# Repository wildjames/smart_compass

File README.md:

# Smart Compass

The product is going to be something similar to the compass in the Pirates of the Caribbean.

It has a ring of LEDs that indicate the direction you need to walk in to get to the place you want to be, which can be other devices in a tracking group, waypoints on a navigation route (e.g. hiking), Atlas Obscura sites for the city you're in, or some location you pinned (e.g. where you parked your car, or something like that).
Locations will be either pins dropped by the compass itself, or loaded to the device using a companion app on a phone - communicating with that means the device needs BLE. The nRF52840 module gives that.

The compass has a GNSS module for getting its own location, and a 9-axis IMU for the compass orientation.
It has a LoRa radio for kilometer-range mesh networking, allowing it to maintain an off-grid communication layer in cases where the cell network is either unavailable (e.g. rural locations, mountains), or overloaded (e.g. music festivals and other large events) - or if you just don't want to be carrying a phone (e.g. a kid being set loose in a shopping centre).

For typical single-device operation, however, the compass will rely on a companion phone app. Using the app, the user can navigate to desired location without referring to their phone. These can be user-defined, like setting the navigation destination on Maps, or get a list of Locations of Interest (LoI) from something like Atlas Obscura. I could also do a "hot/cold" thing with phone RSSI signal strength to get a kind of phone finder feature, but that may not be very useful.

## Design requirements

The device has a few core requirements:

- It must operate with no companion phone or PC. It's fine to have a phone for initial setup, or for additional features, but peer-to-peer operation must be entirely on-device.
- Tracking must be done by the device. The GNSS network must be used for this.
- The device must be secure - there must be no way for non-paired devices to be able to discern the location of a device, even if they are part of the same mesh network.
- Communication between devices must be long-range. Kilometer ranges between peers is a requirement, and longer ranges with a mesh network is also necessary.
- The battery must last for at least a day, but 3 day battery life is the target. Deep sleep, low power, and high polling modes should be used to assist this.
- The device must be handheld. No external antenna is ideal, but the option to add one may be worthwhile.
- The device must have flash storage
- The device needs an on-board way to communicate the direction and distance of paired devices.
  - The device must have a ring of addressable RGB LEDs for peer indication.
  - The device must have a haptic engine for feedback
  - The device may have a speaker for feedback.

I'm writing down user flows as I think of them in the [User Flow Library](UserFlowLibrary.md) page.

-----

## Archived KiCAD packages

- 0.1: First edition.
- 0.2: Submitted to reddit for hope of review. First hierarchical schematic.
- 0.3: Reviewed connections, fixed a few bugs with USB and SPI.
- 0.4: Rerouted the board to place the e-ink connector correctly, and the MCU more centrally. Also made the antenna placement more seriously, with proper clearance zone and via stitching.

-----

## Thoughts

The component cost per device is up to ~£50. The boards are about £5 per board for the first run (some heavy discounts, I shouldn't squander that). Assembled, the first shipment of 5 boards would cost $115 plus ~$60 in components per board makes that up to $400. That's a hefty chunk of cash. I could try getting just two assembled for this initial run, which brings it down to like, $200, but that's still pricey.

## TODO list

- Breaking the LED ring and display out to daughter boards is in progress. The two new schematics exist at [boards/led_ring/](boards/led_ring/) and [boards/display/](boards/display/); see [boards/README.md](boards/README.md) for the interconnect pinouts and what still has to be stripped out of the main board.
  - Similarly, it may be worth breaking the LoRa and GNSS out to a daughter board, which may make the antenna placement easier. Less compelling though, and probably not worth the extra thickness.
- I can apparently use a pi pico 2 as an SWD programmer, to flash the bootloader, and from there I can just upload via the native USB. I need to prove this out though.
- I will do the programming in Rust, using the Embassy ecosystem. This will give me the memory safety and speed of rust (nice when there is no easy way to see crashes on the device), but also the fearless concurrency will be a massive boon with all the ICs that need to be interfaced with.

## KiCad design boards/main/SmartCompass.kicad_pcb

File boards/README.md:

# Board set

The Smart Compass is built as three PCBs. KiCad has no multi-board project, so
each one is its own project directory here, and the parts they share live in
`../libs/`.

| Directory | Project | What it is |
| --------- | ------- | ---------- |
| `main/` | `SmartCompass` | The engine board: MCU, GNSS, LoRa, IMU, flash, power tree, haptics, buttons, USB |
| `led_ring/` | `LedRing` | The 16-LED addressable RGB ring |
| `display/` | `Display` | The e-ink panel connector and its charge-pump support |

The ring and display were split off so the housing can be assembled and
modified without the main board's position dictating where they sit.

Parts that are not on any board - the haptic actuator, the panel, the cell, the
case switches and buttons, the antennas, and the cables and housings joining
them - are listed in [EXTRA_PARTS_BOM.md](EXTRA_PARTS_BOM.md), because they never
appear in a BOM exported from a schematic. Outstanding sourcing work and open
risks are in [COMPONENT_SOURCING.md](COMPONENT_SOURCING.md).

The main board's power tree can be simulated in KiCad's built-in SPICE
simulator; [main/sim/README.md](main/sim/README.md) explains the setup, what is
modelled and excluded, and the results so far. The part models are in
`../libs/spice/`.

## Libraries

`../libs/smart_compass.kicad_sym` and `../libs/smart_compass.pretty` hold the
parts the boards share. They were extracted from the main board, where they had
only ever existed embedded inside the `.kicad_sch` and `.kicad_pcb` files - they
were never in any library table, so a new project could not place them.

Footprints live alongside in `../libs/smart_compass.pretty/`, and 3D models in
`../libs/smart_compass.3dshapes/`.

3D models are referenced from inside the footprint with a
`${KIPRJMOD}/../../libs/smart_compass.3dshapes/...` path
The main board still resolves its other custom parts from its embedded copies,
which is why its ERC reports a long list of "configuration does not include
the symbol library" warnings. Those predate the split. Extracting the rest
into `libs/` would clear them.

Each daughter board has a project-scope `sym-lib-table` and `fp-lib-table`
pointing at `${KIPRJMOD}/../../libs/`, so the paths survive the repo being
cloned somewhere else.

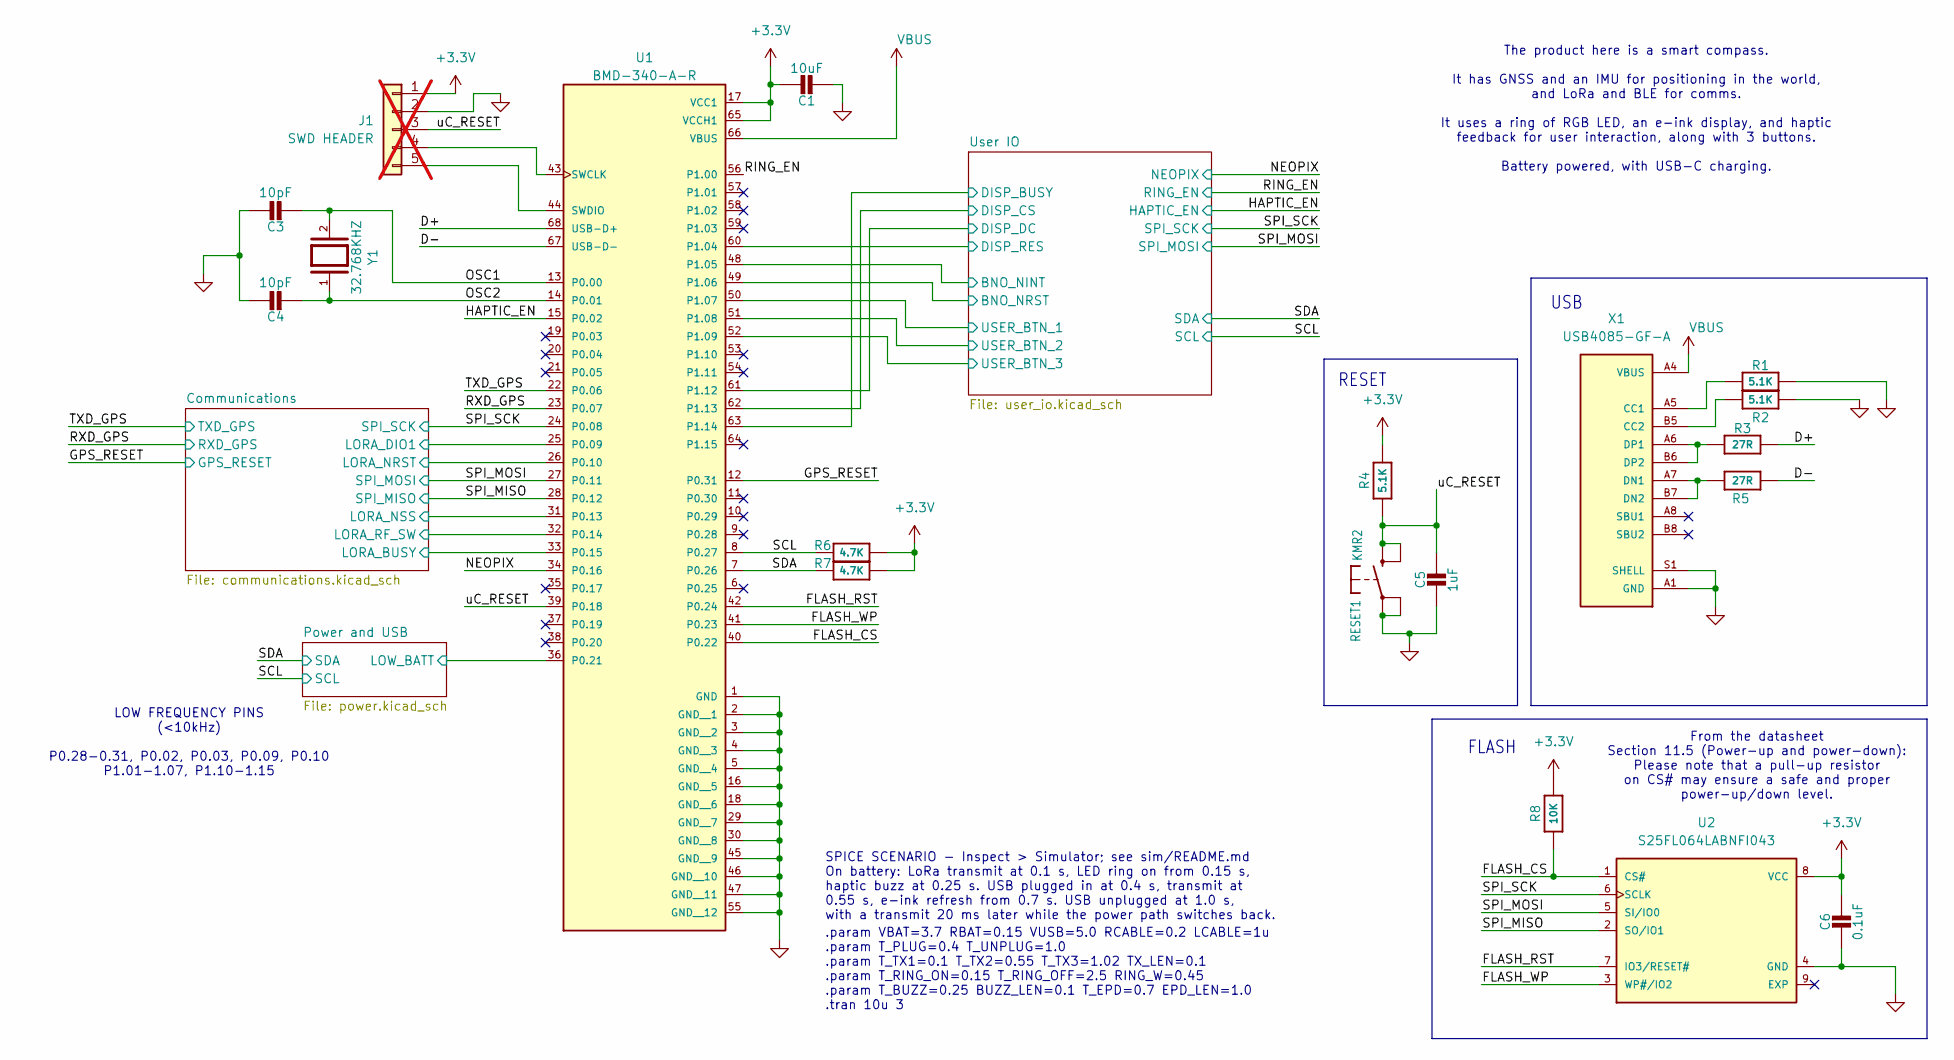
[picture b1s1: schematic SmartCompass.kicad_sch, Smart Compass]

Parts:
C1: 10uF; C_0805_2012Metric; Voltage 10V; MPN CGA4J3X5R1A106K125AB; DigiKey_PN 445-6970-1-ND
C3, C4: 10pF; C_0402_1005Metric; Voltage 50V; MPN CL05C100JB5NNNC; DigiKey_PN 1276-1139-1-ND
C5: 1uF; C_0603_1608Metric; Voltage 50V; Tolerance 10%; MPN C1608X7R1H105K080AB; DigiKey_PN 445-C1608X7R1H105K080ABCT-ND
C6: 0.1uF; C_0402_1005Metric; Voltage 16V; MPN CL05B104KO5VPNC; DigiKey_PN 1276-6844-1-ND
J1: SWD HEADER; PinHeader_1x05_P2.54mm_Vertical; not fitted
R1, R2, R4: 5.1K; R_0603_1608Metric; Tolerance 1%; MPN ERJ-3EKF5101V; DigiKey_PN P5.10KHCT-ND
R3, R5: 27R; R_0603_1608Metric; Tolerance 1%; MPN RC0603FR-0727RL; DigiKey_PN 311-27.0HRCT-ND
R6, R7: 4.7K; R_0603_1608Metric; Tolerance 1%; MPN RC0603FR-074K7L; DigiKey_PN 311-4.70KHRCT-ND
R8: 10K; R_0603_1608Metric; Tolerance 1%; MPN RC0603FR-0710KL; DigiKey_PN 311-10.0KHRCT-ND
RESET1: KMR2; SW_Push_1P1T-SH_NO_CK_KMR2xxG; MPN KMR221NG LFS; DigiKey_PN CKN10244CT-ND
U1: BMD-340-A-R; RIGADO_BMD-340-A-R; MPN BMD-340-A-R; DigiKey_PN 672-BMD-340-A-RCT-ND
U2: S25FL064LABNFI043; SON80P400X400X60-9N; MPN S25FL064LABNFI043; DigiKey_PN 448-S25FL064LABNFI043CT-ND
X1: USB4085-GF-A; GCT_USB4085-GF-A_REVA4; MPN USB4085-GF-A; DigiKey_PN 2073-USB4085-GF-ACT-ND
Y1: 32.768KHZ; XTAL_ABS07-32.768KHZ-7-T; PARTREV 08.19.15; DigiKey_PN 535-9543-1-ND

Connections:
+3.3V: C1.1, C6.1, J1.1, R4.2, R6.1, R7.1, R8.2, U1.17 (VCC1), U1.65 (VCCH1), U2.8 (VCC); also elsewhere on the board
/Communications/LORA_BUSY: U1.33 (P0.15); also elsewhere on the board
/Communications/LORA_DIO1: U1.25 (P0.09); also elsewhere on the board
/Communications/LORA_NRST: U1.26 (P0.10); also elsewhere on the board
/Communications/LORA_NSS: U1.31 (P0.13); also elsewhere on the board
/Communications/LORA_RF_SW: U1.32 (P0.14); also elsewhere on the board
/D+: R3.1, U1.68 (USB-D+)
/D-: R5.1, U1.67 (USB-D-)
/FLASH_CS: R8.1, U1.40 (P0.22), U2.1 (CS#)
/FLASH_RST: U1.42 (P0.24), U2.7 (IO3/RESET#)
/FLASH_WP: U1.41 (P0.23), U2.3 (WP#/IO2)
/GPS_RESET: U1.12 (P0.31); also elsewhere on the board
/HAPTIC_EN: U1.15 (P0.02); also elsewhere on the board
/NEOPIX: U1.34 (P0.16); also elsewhere on the board
/OSC1: C3.2, U1.13 (P0.00), Y1.2
/OSC2: C4.2, U1.14 (P0.01), Y1.1
/Power and USB/LOW_BATT: U1.36 (P0.21); also elsewhere on the board
/RING_EN: U1.56 (P1.00); also elsewhere on the board
/RXD_GPS: U1.23 (P0.07); also elsewhere on the board
/SCL: R6.2, U1.8 (P0.27); also elsewhere on the board
/SDA: R7.2, U1.7 (P0.26); also elsewhere on the board
/SPI_MISO: U1.28 (P0.12), U2.2 (SO/IO1); also elsewhere on the board
/SPI_MOSI: U1.27 (P0.11), U2.5 (SI/IO0); also elsewhere on the board
/SPI_SCK: U1.24 (P0.08), U2.6 (SCLK); also elsewhere on the board
/TXD_GPS: U1.22 (P0.06); also elsewhere on the board
/User IO/BNO_NINT: U1.48 (P1.05); also elsewhere on the board
/User IO/BNO_NRST: U1.49 (P1.06); also elsewhere on the board
/User IO/DISP_BUSY: U1.63 (P1.14); also elsewhere on the board
/User IO/DISP_CS: U1.62 (P1.13); also elsewhere on the board
/User IO/DISP_DC: U1.61 (P1.12); also elsewhere on the board
/User IO/DISP_RES: U1.60 (P1.04); also elsewhere on the board
/User IO/USER_BTN_1: U1.50 (P1.07); also elsewhere on the board
/User IO/USER_BTN_2: U1.51 (P1.08); also elsewhere on the board
/User IO/USER_BTN_3: U1.52 (P1.09); also elsewhere on the board
/uC_RESET: C5.1, J1.3, R4.1, RESET1.2, U1.39 (P0.18)
GND: C1.2, C3.1, C4.1, C5.2, C6.2, J1.2, R1.1, R2.1, RESET1.1, U1.1 (GND), U1.2 (GND__1), U1.3 (GND__2), U1.4 (GND__3), U1.5 (GND__4), U1.16 (GND__5), U1.18 (GND__6), U1.29 (GND__7), U1.30 (GND__8), U1.45 (GND__9), U1.46 (GND__10), U1.47 (GND__11), U1.55 (GND__12), U2.4 (GND), X1.A1 (GND), X1.A12 (GND), X1.B1 (GND), X1.B12 (GND), X1.S1 (SHELL), X1.S2 (SHELL), X1.S3 (SHELL), X1.S4 (SHELL); also elsewhere on the board
unnamed: J1.4, U1.43 (SWCLK)
unnamed: J1.5, U1.44 (SWDIO)
unnamed: R1.2, X1.A5 (CC1)
unnamed: R2.2, X1.B5 (CC2)
unnamed: R5.2, X1.A7 (DN1), X1.B7 (DN2)
unnamed: R3.2, X1.A6 (DP1), X1.B6 (DP2)
VBUS: U1.66 (VBUS), X1.A4 (VBUS), X1.A9 (VBUS), X1.B4 (VBUS), X1.B9 (VBUS); also elsewhere on the board

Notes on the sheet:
From the datasheet Section 11.5 (Power-up and power-down): Please note that a pull-up resistor on CS# may ensure a safe and proper power-up/down level.
FLASH
The product here is a smart compass. It has GNSS and an IMU for positioning in the world, and LoRa and BLE for comms. It uses a ring of RGB LED, an e-ink display, and haptic feedback for user interaction, along with 3 buttons. Battery powered, with USB-C charging.
LOW FREQUENCY PINS (<10kHz) P0.28-0.31, P0.02, P0.03, P0.09, P0.10 P1.01-1.07, P1.10-1.15
RESET
SPICE SCENARIO - Inspect > Simulator; see sim/README.md On battery: LoRa transmit at 0.1 s, LED ring on from 0.15 s, haptic buzz at 0.25 s. USB plugged in at 0.4 s, transmit at 0.55 s, e-ink refresh from 0.7 s. USB unplugged at 1.0 s, with a transmit 20 ms later while the power path switches back.
USB
.param VBAT=3.7 RBAT=0.15 VUSB=5.0 RCABLE=0.2 LCABLE=1u .param T_PLUG=0.4 T_UNPLUG=1.0 .param T_TX1=0.1 T_TX2=0.55 T_TX3=1.02 TX_LEN=0.1 .param T_RING_ON=0.15 T_RING_OFF=2.5 RING_W=0.45 .param T_BUZZ=0.25 BUZZ_LEN=0.1 T_EPD=0.7 EPD_LEN=1.0 .tran 10u 3

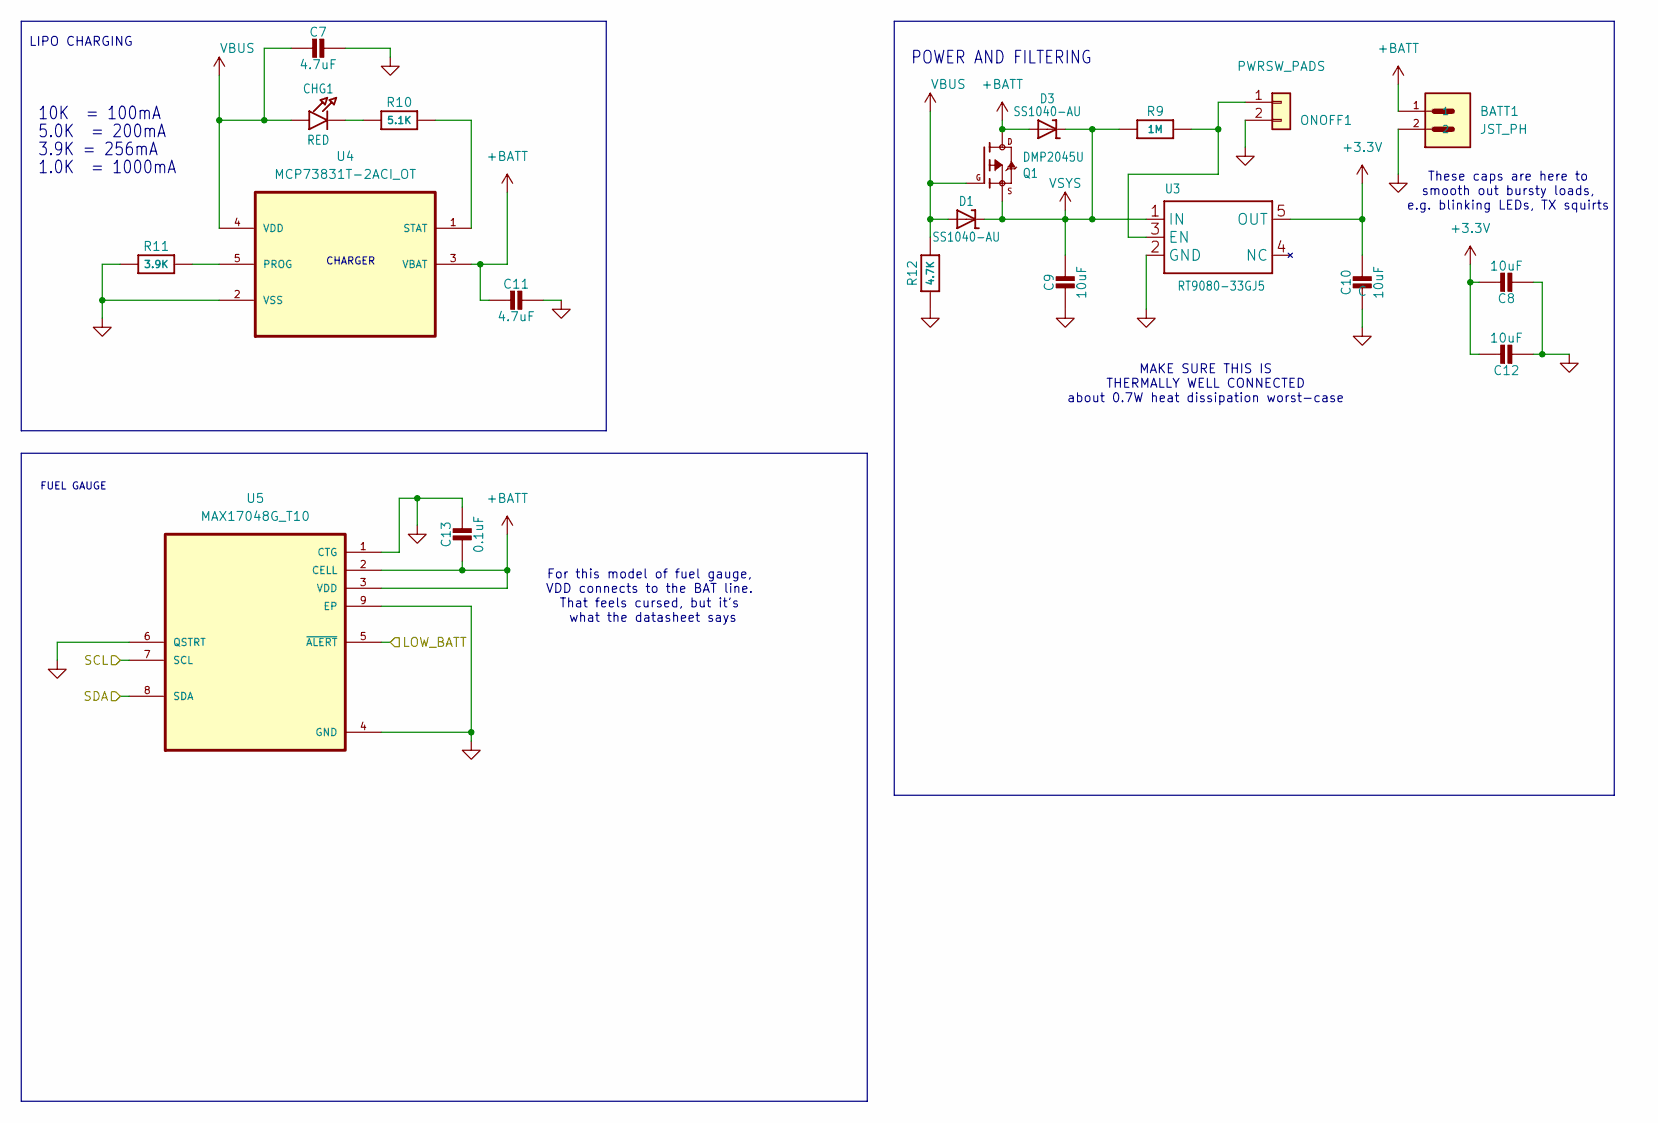
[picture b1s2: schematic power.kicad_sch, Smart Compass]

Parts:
BATT1: JST_PH; JST_S2B-PH-SM4-TB; MPN S2B-PH-SM4-TB; DigiKey_PN 455-S2B-PH-SM4-TBCT-ND
C7, C11: 4.7uF; C_1206_3216Metric; Voltage 50V; Tolerance 10%; MPN CL31B475KBHNFNE; DigiKey_PN 1276-3179-1-ND
C8, C9, C10, C12: 10uF; C_0805_2012Metric; Voltage 10V; MPN CGA4J3X5R1A106K125AB; DigiKey_PN 445-6970-1-ND
C13: 0.1uF; C_0402_1005Metric; Voltage 16V; MPN CL05B104KO5VPNC; DigiKey_PN 1276-6844-1-ND
CHG1: RED; LED_0603_1608Metric; MPN LTST-C191KRKT; DigiKey_PN 160-1447-1-ND
D1, D3: SS1040-AU; D_SOD-123; MPN SS1040-AU_R1_000A1; DigiKey_PN 3757-SS1040-AU_R1_000A1CT-ND
ONOFF1: PWRSW_PADS; SolderWire-0.127sqmm_1x02_P3.7mm_D0.48mm_OD1mm_Relief
Q1: DMP2045U; SOT-23; MPN DMP2045U-7; DigiKey_PN DMP2045U-7DICT-ND
R9: 1M; R_0603_1608Metric; Tolerance 1%; MPN RC0603FR-071ML; DigiKey_PN 311-1.00MHRCT-ND
R10: 5.1K; R_0603_1608Metric; Tolerance 1%; MPN ERJ-3EKF5101V; DigiKey_PN P5.10KHCT-ND
R11: 3.9K; R_0603_1608Metric; Tolerance 1%; MPN RC0603FR-073K9L; DigiKey_PN 311-3.90KHRCT-ND
R12: 4.7K; R_0603_1608Metric; Tolerance 1%; MPN RC0603FR-074K7L; DigiKey_PN 311-4.70KHRCT-ND
U3: RT9080-33GJ5; SOT94P280X100-5N; MPN RT9080-33GJ5; DigiKey_PN 1028-1509-1-ND
U4: MCP73831T-2ACI_OT; SOT95P280X145-5N; MPN MCP73831T-2ACI/OT; DigiKey_PN MCP73831T-2ACI/OTCT-ND
U5: MAX17048G_T10; SON50P200X200X80-9N; MPN MAX17048G+T10; DigiKey_PN MAX17048G+T10CT-ND

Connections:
+3.3V: C8.1, C10.1, C12.1, U3.5 (OUT); also elsewhere on the board
+BATT: BATT1.1, C11.2, C13.2, D3.2 (A), Q1.3 (D), U4.3 (VBAT), U5.2 (CELL), U5.3 (VDD)
/Power and USB/LOW_BATT: U5.5 (~ALERT); also elsewhere on the board
/SCL: U5.7 (SCL); also elsewhere on the board
/SDA: U5.8 (SDA); also elsewhere on the board
GND: BATT1.2, C7.1, C8.2, C9.2, C10.2, C11.1, C12.2, C13.1, ONOFF1.2, R11.1, R12.2, U3.2 (GND), U4.2 (VSS), U5.1 (CTG), U5.4 (GND), U5.6 (QSTRT), U5.9 (EP); also elsewhere on the board
unnamed: CHG1.1, R10.1
unnamed: ONOFF1.1, R9.2, U3.3 (EN)
unnamed: R11.2, U4.5 (PROG)
unnamed: R10.2, U4.1 (STAT)
VBUS: C7.2, CHG1.2, D1.2 (A), Q1.1 (G), R12.1, U4.4 (VDD); also elsewhere on the board
VSYS: C9.1, D1.1 (K), D3.1 (K), Q1.2 (S), R9.1, U3.1 (IN); also elsewhere on the board

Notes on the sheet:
10K = 100mA
POWER AND FILTERING
CHARGER
1.0K = 1000mA
5.0K = 200mA
MAKE SURE THIS IS THERMALLY WELL CONNECTED about 0.7W heat dissipation worst-case
3.9K = 256mA
LIPO CHARGING
These caps are here to smooth out bursty loads, e.g. blinking LEDs, TX squirts
For this model of fuel gauge, VDD connects to the BAT line. That feels cursed, but it's what the datasheet says
FUEL GAUGE

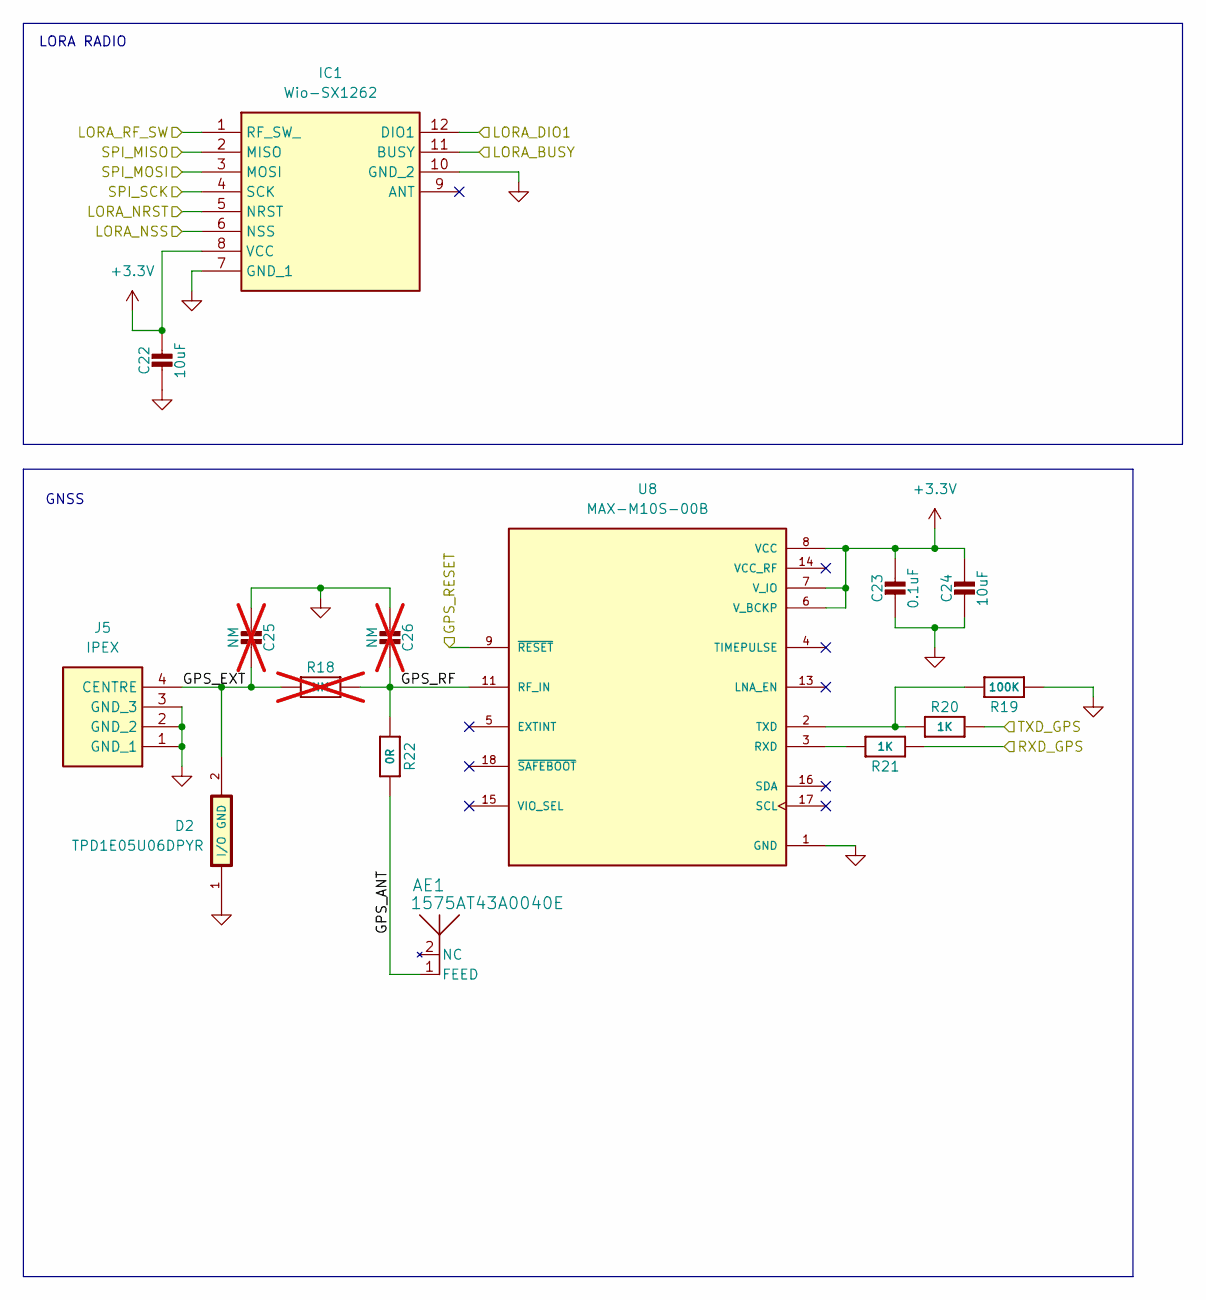
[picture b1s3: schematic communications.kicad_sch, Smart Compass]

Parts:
AE1: 1575AT43A0040E; ANT_1575AT_JOT; MPN 1575AT43A0040001E; DigiKey_PN 712-1575AT43A0040001ECT-ND
C22, C24: 10uF; C_0805_2012Metric; Voltage 10V; MPN CGA4J3X5R1A106K125AB; DigiKey_PN 445-6970-1-ND
C23: 0.1uF; C_0402_1005Metric; Voltage 16V; MPN CL05B104KO5VPNC; DigiKey_PN 1276-6844-1-ND
C25, C26: NM; C_0402_1005Metric; MPN DNP; not fitted
D2: TPD1E05U06DPYR; DIO_TPD1E05U06DPYR; MPN TPD1E05U06DPYR; DigiKey_PN 296-39341-1-ND
IC1: Wio-SX1262; MODULE12P-1.27-11X11.6MM; Mouser Part Number 713-114993390
J5: IPEX; SMT_9.001E.01_TAL; Mouser Part Number 960-RECE.20369001E01
R18: NM; R_0603_1608Metric; MPN DNP; not fitted
R19: 100K; R_0603_1608Metric; Tolerance 1%; MPN RC0603FR-07100KL; DigiKey_PN 311-100KHRCT-ND
R20, R21: 1K; R_0603_1608Metric; Tolerance 1%; MPN RC0603FR-071KL; DigiKey_PN 311-1.00KHRCT-ND
R22: 0R; R_0603_1608Metric; Tolerance Jumper; MPN RC0603JR-070RL; DigiKey_PN 311-0.0GRCT-ND
U8: MAX-M10S-00B; XCVR_MAX-M10S-00B; PARTREV C1; DigiKey_PN 672-MAX-M10S-00BCT-ND

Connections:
+3.3V: C22.1, C23.1, C24.1, IC1.8 (VCC), U8.6 (V_BCKP), U8.7 (V_IO), U8.8 (VCC); also elsewhere on the board
/Communications/GPS_ANT: AE1.1 (FEED_1), R22.2
/Communications/GPS_EXT: C25.1, D2.2 (GND), J5.4 (CENTRE), R18.1
/Communications/GPS_RF: C26.1, R18.2, R22.1, U8.11 (RF_IN)
/Communications/LORA_BUSY: IC1.11 (BUSY); also elsewhere on the board
/Communications/LORA_DIO1: IC1.12 (DIO1); also elsewhere on the board
/Communications/LORA_NRST: IC1.5 (NRST); also elsewhere on the board
/Communications/LORA_NSS: IC1.6 (NSS); also elsewhere on the board
/Communications/LORA_RF_SW: IC1.1 (RF_SW_); also elsewhere on the board
/GPS_RESET: U8.9 (~RESET); also elsewhere on the board
/RXD_GPS: R21.2; also elsewhere on the board
/SPI_MISO: IC1.2 (MISO); also elsewhere on the board
/SPI_MOSI: IC1.3 (MOSI); also elsewhere on the board
/SPI_SCK: IC1.4 (SCK); also elsewhere on the board
/TXD_GPS: R20.1; also elsewhere on the board
GND: C22.2, C23.2, C24.2, C25.2, C26.2, D2.1 (I/O), IC1.7 (GND_1), IC1.10 (GND_2), J5.1 (GND_1), J5.2 (GND_2), J5.3 (GND_3), R19.2, U8.1 (GND), U8.10 (GND), U8.12 (GND); also elsewhere on the board
unnamed: R21.1, U8.3 (RXD)
unnamed: R19.1, R20.2, U8.2 (TXD)

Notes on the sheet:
LORA RADIO
GNSS

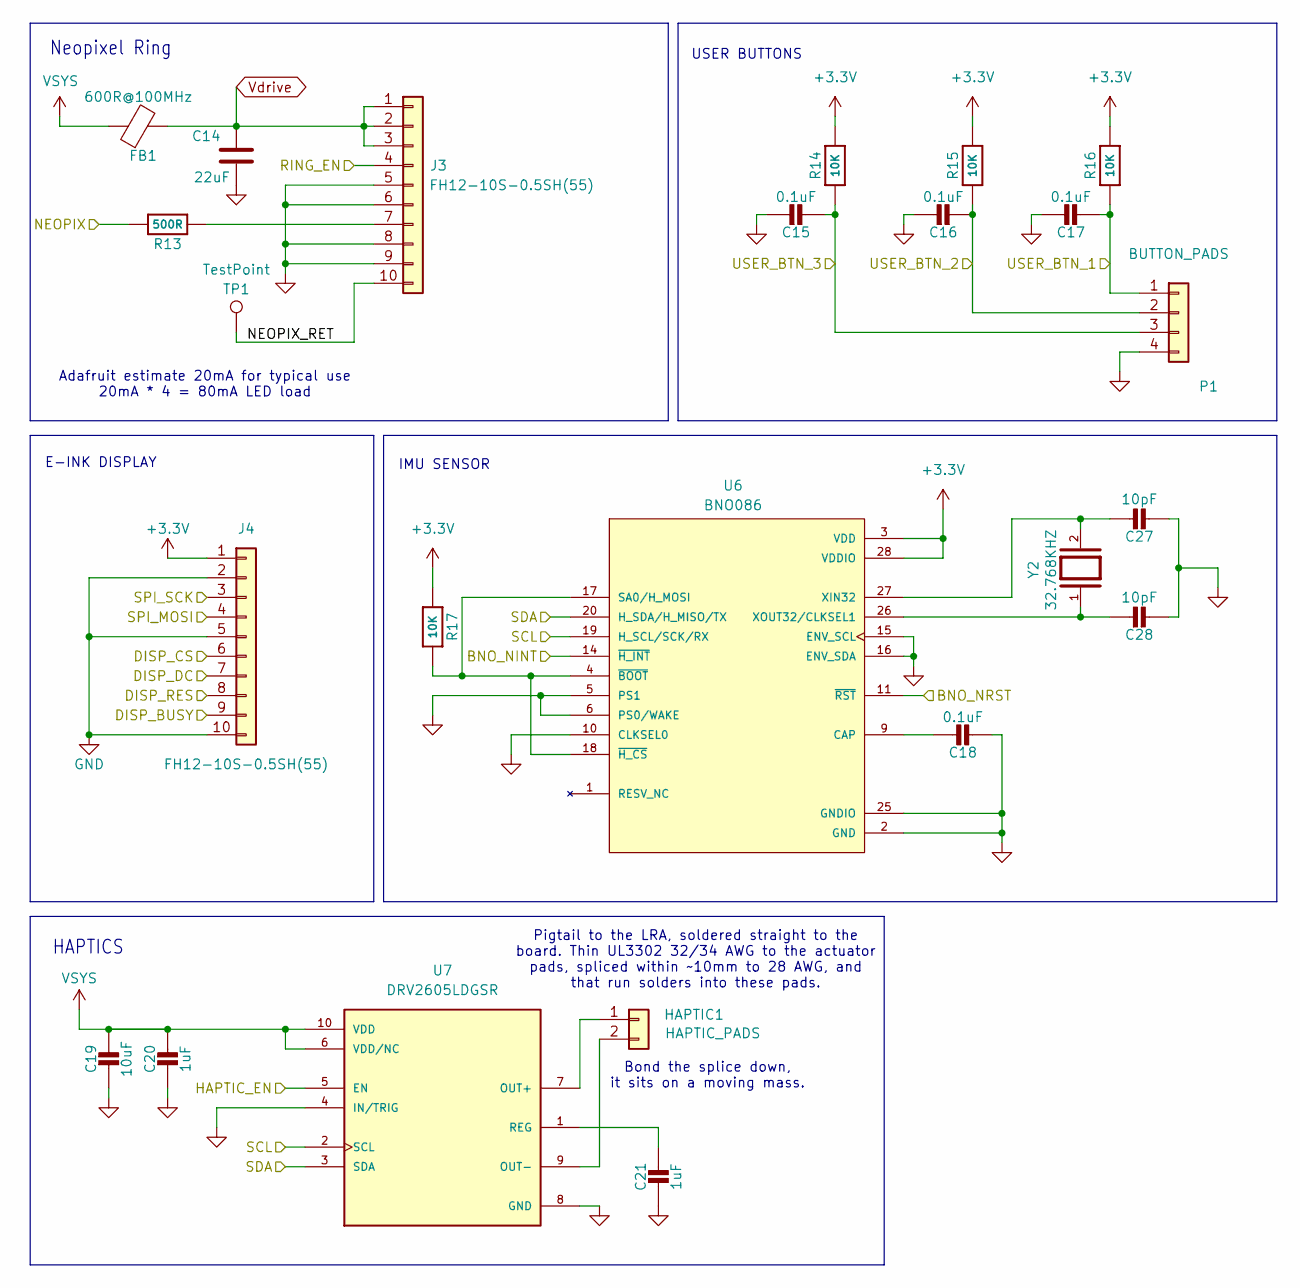
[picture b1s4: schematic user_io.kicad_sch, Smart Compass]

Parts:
C14: 22uF; C_0805_2012Metric; Voltage 10V; MPN CL21A226KPCLRNC; DigiKey_PN 1276-6786-1-ND
C15, C16, C17, C18: 0.1uF; C_0402_1005Metric; Voltage 16V; MPN CL05B104KO5VPNC; DigiKey_PN 1276-6844-1-ND
C19: 10uF; C_0805_2012Metric; Voltage 10V; MPN CGA4J3X5R1A106K125AB; DigiKey_PN 445-6970-1-ND
C20, C21: 1uF; C_0603_1608Metric; Voltage 50V; Tolerance 10%; MPN C1608X7R1H105K080AB; DigiKey_PN 445-C1608X7R1H105K080ABCT-ND
C27, C28: 10pF; C_0402_1005Metric; Voltage 50V; MPN CL05C100JB5NNNC; DigiKey_PN 1276-1139-1-ND
FB1: 600R@100MHz; L_0603_1608Metric; MPN MPZ1608S601ATA00; DigiKey_PN 445-MPZ1608S601ATA00CT-ND
HAPTIC1: HAPTIC_PADS; SolderWire-0.127sqmm_1x02_P3.7mm_D0.48mm_OD1mm_Relief
J3, J4: FH12-10S-0.5SH(55); Hirose_FH12-10S-0.5SH_1x10-1MP_P0.50mm_Horizontal; MPN FH12-10S-0.5SH(55); DigiKey_PN HFJ110CT-ND
P1: BUTTON_PADS; SolderWire-0.127sqmm_1x04_P3.7mm_D0.48mm_OD1mm_Relief
R13: 500R; R_0603_1608Metric; Tolerance 0.1%; MPN RT0603BRC07500RL; DigiKey_PN 13-RT0603BRC07500RLCT-ND
R14, R15, R16, R17: 10K; R_0603_1608Metric; Tolerance 1%; MPN RC0603FR-0710KL; DigiKey_PN 311-10.0KHRCT-ND
TP1: TestPoint; TestPoint_Pad_D1.5mm
U6: BNO086; IC_BNO086; PARTREV v1.17; DigiKey_PN 1888-BNO086CT-ND
U7: DRV2605LDGSR; SOP50P490X110-10N; PARTREV D; DigiKey_PN 296-40032-1-ND
Y2: 32.768KHZ; XTAL_ABS07-32.768KHZ-7-T; PARTREV 08.19.15; DigiKey_PN 535-9543-1-ND

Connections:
+3.3V: J4.1, R14.2, R15.2, R16.2, R17.2, U6.3 (VDD), U6.28 (VDDIO); also elsewhere on the board
/HAPTIC_EN: U7.5 (EN); also elsewhere on the board
/NEOPIX: R13.2; also elsewhere on the board
/RING_EN: J3.4; also elsewhere on the board
/SCL: U6.19 (H_SCL/SCK/RX), U7.2 (SCL); also elsewhere on the board
/SDA: U6.20 (H_SDA/H_MISO/TX), U7.3 (SDA); also elsewhere on the board
/SPI_MOSI: J4.4; also elsewhere on the board
/SPI_SCK: J4.3; also elsewhere on the board
/User IO/BNO_NINT: U6.14 (~H_INT); also elsewhere on the board
/User IO/BNO_NRST: U6.11 (~RST); also elsewhere on the board
/User IO/DISP_BUSY: J4.9; also elsewhere on the board
/User IO/DISP_CS: J4.6; also elsewhere on the board
/User IO/DISP_DC: J4.7; also elsewhere on the board
/User IO/DISP_RES: J4.8; also elsewhere on the board
/User IO/NEOPIX_RET: J3.10, TP1.1 (1_1)
/User IO/USER_BTN_1: C17.2, P1.1, R16.1; also elsewhere on the board
/User IO/USER_BTN_2: C16.2, P1.2, R15.1; also elsewhere on the board
/User IO/USER_BTN_3: C15.2, P1.3, R14.1; also elsewhere on the board
GND: C14.2, C15.1, C16.1, C17.1, C18.2, C19.2, C20.2, C21.2, C27.1, C28.1, J3.5, J3.6, J3.8, J3.9, J4.2, J4.5, J4.10, P1.4, U6.2 (GND), U6.5 (PS1), U6.6 (PS0/WAKE), U6.10 (CLKSEL0), U6.15 (ENV_SCL), U6.16 (ENV_SDA), U6.25 (GNDIO), U7.4 (IN/TRIG), U7.8 (GND); also elsewhere on the board
unnamed: HAPTIC1.1, U7.7 (OUT+)
unnamed: HAPTIC1.2, U7.9 (OUT-)
unnamed: J3.7, R13.1
unnamed: C18.1, U6.9 (CAP)
unnamed: R17.1, U6.4 (~BOOT), U6.17 (SA0/H_MOSI), U6.18 (~H_CS)
unnamed: C27.2, U6.27 (XIN32), Y2.2
unnamed: C28.2, U6.26 (XOUT32/CLKSEL1), Y2.1
unnamed: C21.1, U7.1 (REG)
VSYS: C19.1, C20.1, FB1.1, U7.6 (VDD/NC), U7.10 (VDD); also elsewhere on the board
Vdrive: C14.1, FB1.2, J3.1, J3.2, J3.3

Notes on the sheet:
Neopixel Ring
USER BUTTONS
E-INK DISPLAY
Adafruit estimate 20mA for typical use 20mA * 4 = 80mA LED load
Pigtail to the LRA, soldered straight to the board. Thin UL3302 32/34 AWG to the actuator pads, spliced within ~10mm to 28 AWG, and that run solders into these pads.
IMU SENSOR
HAPTICS
Bond the splice down, it sits on a moving mass.

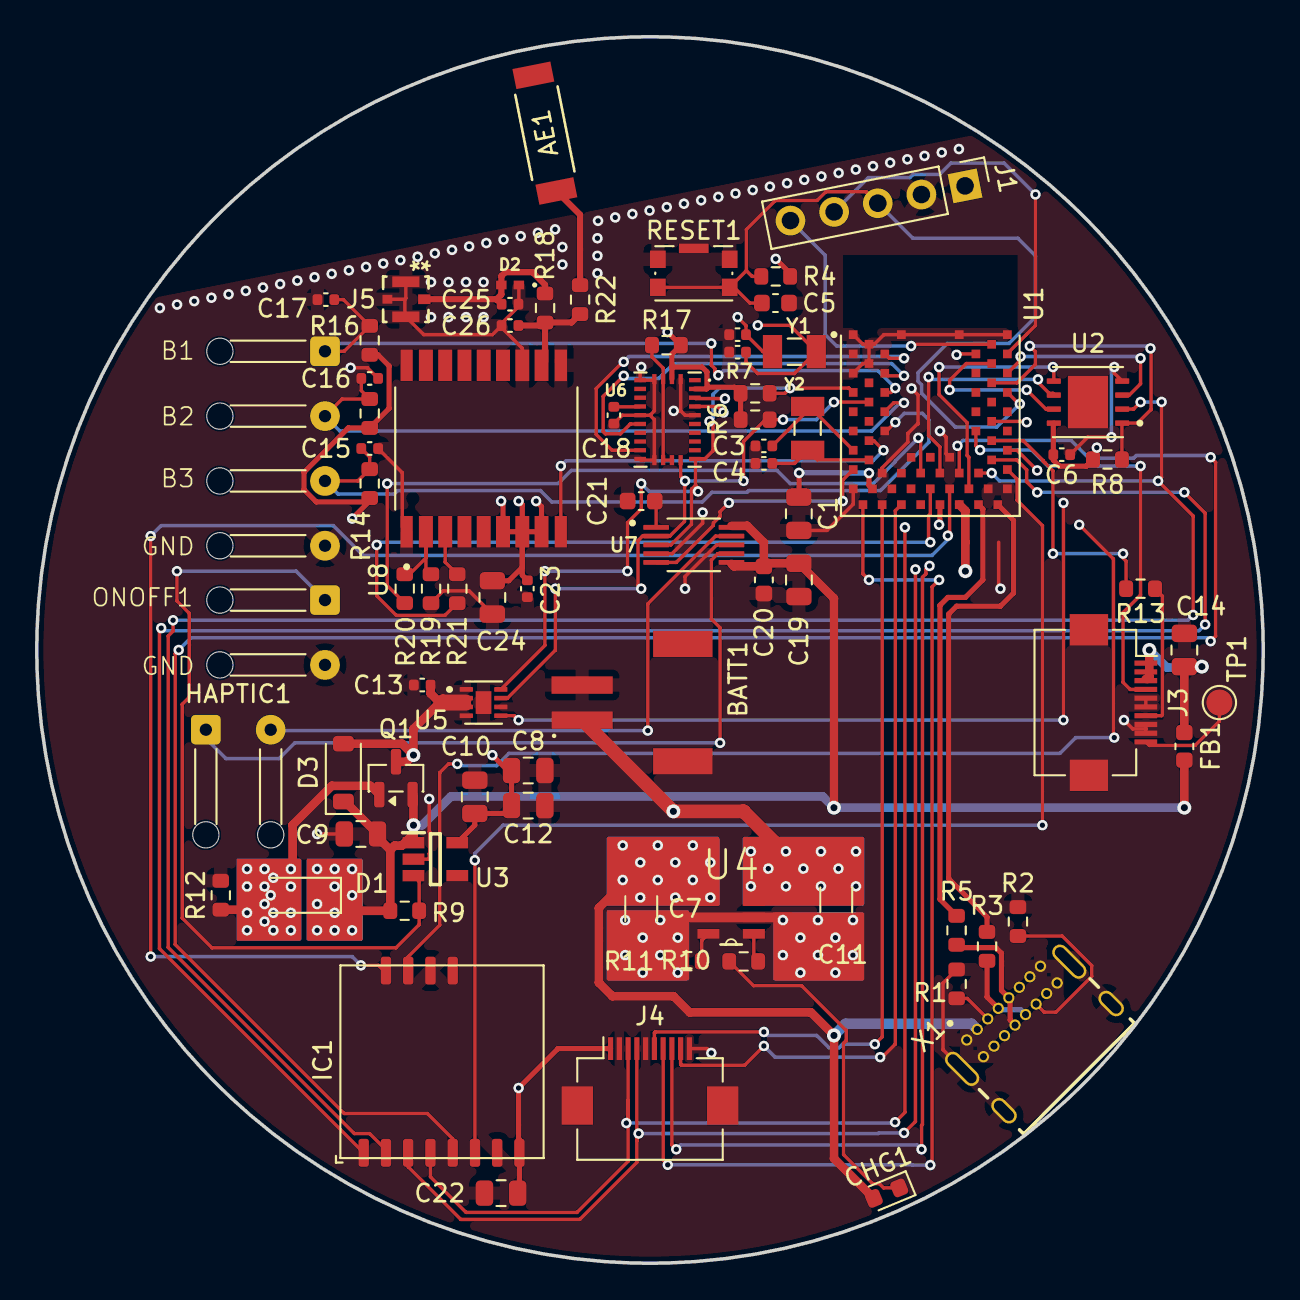
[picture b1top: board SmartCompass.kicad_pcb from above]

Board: 4 copper layers, 70.0 x 70.0 mm, 78 parts (0 on the bottom side), 64 nets.
